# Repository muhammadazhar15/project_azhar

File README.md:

# [project_azhar](https://github.com/muhammadazhar15/project_azhar)
Collection of projects that have been made!

# [PROJECT 1: Soccer Robot Localization Based on Sensor Fusion from Odometry and Omnivision](Project1-robot_localization)

<div align="center">

</div>
  
* This research aims to create a new robot localization system for [IRIS ITS](https://iris.its.ac.id/) robots in the soccer field
* This localization system combines Odometry and Particle Filter through sensor fusion method
* Odometry uses 2 encoder sensors and a gyro sensor to sense robot displacement
* Particle Filter use omnivision as visual sensor to detect white line in the soccer field through image processing
* For more complete explanation about this research, you can check [this](Project1-robot_localization/Paper)

> **This is my early research particle filter with python**
> 
> https://user-images.githubusercontent.com/120243882/213215666-4653b4f7-5cf8-48bd-91ea-d05469076f68.mp4
> * if you want try this program you can check [this](Project1-robot_localization/Prototype_particle_filter)

> **This is particle filter that applied to the soccer robot**
> 
> https://user-images.githubusercontent.com/120243882/213215766-411f6838-0309-486a-b52c-df728a80d029.mp4

> **This is final localization system with senor fusion**
> 
> https://user-images.githubusercontent.com/120243882/213237570-8e828789-f15e-48b3-8e15-77b1aa8b0c28.mp4
> * The red line is the localization data generated by sensor fusion
> * This video compare sensor fusion data with original robot location in the soccer field

# [PROJECT 2: Voice Recognition System for Commands on Wheeled Soccer Robots](Project2-voice_command)

<div align="center">
 
 &nbsp;&nbsp;&nbsp;&nbsp;&nbsp;&nbsp;&nbsp;&nbsp;&nbsp;&nbsp;&nbsp;&nbsp;&nbsp;
   
</div>

* This research conducted to give [IRIS ITS](https://iris.its.ac.id/) soccer robots some orders through human voice
* There are 2 main processes in this voice recognition system, record and recognition
* This research use CNN (Convolutional Neural Network) to recognize commands from human voice
* There are 7 commands that can be recognized ['Corner', 'Dropball', 'Goalkick', 'Kalibrasi', 'Kickoff', 'Stop', 'Tendang']
* In this research MFCC is used as feature extraction method to process data from human voice
* Data that used in CNN training process comes from 5 different people and 9 different people for test
* For more complete explanation about this research, you can check [this](Project2-voice_command/Paper)

> **Those are some visualization data from voice signal data and MFCC feature extraction results**
> 
> 

> **Voice Commands Demo for Soccer Robot**
> 
> https://user-images.githubusercontent.com/120243882/213928835-b99e419a-455b-4ef3-9824-324b2552bdfb.mp4

# [PROJECT 3: Heart Disease Detection System with ANN (Artificial Neural Network)](Project3-heart_disease_detector)

<div align="center">
 
 &nbsp;&nbsp;&nbsp;&nbsp;&nbsp;&nbsp;&nbsp;&nbsp;
 
</div>

* Research project while teaching at [MA Darussalam Jombang](https://emispendis.kemenag.go.id/dashboard/?content=madrasah&action=lbg&nss=131235170053)
* Introducing AI (Artificial Intelligence) to Madrasah students, especially about Neural Networks
* This research was conducted with students to prepare for participate in [LKIR LIPI](https://kompetisi.brin.go.id/tentang/lkir) 2021
* Heart Disease Detection System is designed to detect disease through health status and heart sounds
* Health status data comes from [Kaggle](https://www.kaggle.com/datasets/johnsmith88/heart-disease-dataset) and heart sound data comes from [here](http://www.peterjbentley.com/heartchallenge/)
* The Heart Disease Detection System is applied in the website
* For more complete explanation about this research, you can check [this](Project3-heart_disease_detector/Paper)

> **Heart Disease Detection System Demo**
> 
> https://user-images.githubusercontent.com/120243882/213934320-be85940c-d860-4ea4-b8dd-51fb7ff6c627.mp4

# [PROJECT 4: Line Follower Robot Microcontroller](Project4-robot_line_follower)

<div align="center">
 
 &nbsp;&nbsp;&nbsp;&nbsp;&nbsp;
 
</div>

* This project is used to introduce students in [MA Darussalam Jombang](https://emispendis.kemenag.go.id/dashboard/?content=madrasah&action=lbg&nss=131235170053) about embedded systems and robotics
* This robot uses Arduino nano as microcontroller and use C/C++ programming language in Arduino IDE
* There are 3 main board in this robot: Sensor, Core, and Driver
* This line followe use 14 line sensors (consist a pair of LED and Photodiode) with switching method, only need 7 ADC to read sensors data
* In Core board, there are buttons, lcd crystal, Arduino nano, and voltage regulator to supply the required voltage for entire robotic system
* DC motor driver is used to control motors rotation, to control 2 motors need 8 MOSFET and 4 BJT Transistors

> **PCB Design for Line Sensors, Core, and DC Motor driver**
> 
> <div align="center">
>  
>  &nbsp;
>  
>  &nbsp;
>  
> </div>
> 
> * For this PCB design, you can check schematic and board with EAGLE [here](Project4-robot_line_follower/Design_PCB)
> * For simple mechanical design of this robot you can check [here](Project4-robot_line_follower/Design_mechanic)

> **Line Follower Robot Microcontroller Demo**
> 
> https://user-images.githubusercontent.com/120243882/213953569-85fc9a23-e856-4095-a18f-c3753762ad43.mp4
> * This robot can be programmed to go through certain tracks such as intersections, incline, black or white line
> * This robot also participate in [MRC 2020](https://madrasah.kemenag.go.id/mrc2020/) 

# [PROJECT 5: Transporter Robot IoT](Project5-robot_transporter_IoT)

<div align="center">
 
 &nbsp;&nbsp;&nbsp;&nbsp;
 
</div>

* This project is used to teach students before participate in [MRC 2021](https://madrasah.kemenag.go.id/mrc2021/) competition
* This Transporter Robot uses ESP32 as microcontroller and can be programmed with Arduino IDE
* Components of Transporter Robot IoT

  <table>
    <tr>
     <td>ESP32</td>
     <td>TCS3200</td>
     <td>GM66</td>
     <td>OLED 128x64</td>
     <td>Gripper Servo</td>
    </tr>
    <tr>
     <td>Line Sensor</td>
     <td>Voltage Regulator</td>
     <td>Driver Motor</td>
     <td>Gearbox Motor</td>
     <td>Lipo battery 12v</td>
    </tr>
  </table>

* There are 3 sensors used by this robot: 2 Line sensor, Barcode Sensor GM66, and Color Sensor TCS3200
* Robot mission is scaning object barcode and then send object to drop location with same barcode
* This robot also send reports about activities that have been carried out such as take the object, drop the object, and object barcode
* The report send through MQTT protocol to this [MQTT Broker Websockets](http://www.hivemq.com/demos/websocket-client/)
* You can check some simple program used to access each sensor [here](Project5-robot_transporter_IoT/Program/trial_program) and program for the entire robot system [here](Project5-robot_transporter_IoT/Program/robot)

> **Transporter Robot IoT Demo**
> 
> https://user-images.githubusercontent.com/120243882/213965095-ef7a9108-83d1-48a8-8197-9af46c50bce0.mp4

# [PROJECT 6: Smart Home IoT](Project6-smart_home_IoT)

<div align="center">
 
</div>

* This is IoT simple project to control some devices with human voice through Google Assistant
* IoT systems consist of:

  <table>
    <tr>
     <th><a href="http://esp32.net/">ESP32</a></th>
     <th><a href="https://blynk.io/">Blynk</a></th>
     <th><a href="https://ifttt.com/">IFTTT</a></th>
     <th><a href="https://assistant.google.com/">Google Assistant</a></th>
    </tr>
  </table>
  
* This project uses relay as actuator which controlled by ESP32 with Blynk interface
* IFTTT as third party, works to make connection between Blynk and Google Assistant
* Arduino IDE program for this project in [here](Project6-smart_home_IoT/Program)
* If you need more clear explanation and illustration about this system, check [here](Project6-smart_home_IoT/System_design)

> **Smart Home IoT Demo**
> 
> https://user-images.githubusercontent.com/120243882/213970831-5661dd2b-66af-45b9-8b20-814e55da1675.mp4

# [PROJECT 7: Teaching Robotics](Project7-teaching_robotics)
* These are some electronics projects that i made while teaching at MA Darussalam Jombang

<div align="center">
 
 &nbsp;&nbsp;&nbsp;&nbsp;&nbsp;&nbsp;&nbsp;&nbsp;&nbsp;&nbsp;&nbsp;&nbsp;&nbsp;&nbsp;&nbsp;&nbsp;&nbsp;&nbsp;&nbsp;&nbsp;&nbsp;&nbsp;&nbsp;&nbsp;&nbsp;&nbsp;&nbsp;
 
</div>

&nbsp;

<div align="center">
 
 &nbsp;&nbsp;
 
</div>

&nbsp;

* Flip-flop, Line sensor, Line Follower Analog, Radio Receiver, Arduino Learning Board, and Simple Motor Driver
* The purpose of these projects are to introduce students about electronics and simple robotics
* These are handbooks that I use to teach, check [here](Project7-teaching_robotics/Handbook)
* These are some collections of PCB designs that I have created to teach, check [here](Project7-teaching_robotics/Design_PCB)

# [PROJECT 8: STM32 Projects Collection](Project6-smart_home_IoT)
* These are some STM32 programming with STM32CubeMX that I had made while joining [IRIS ITS](https://iris.its.ac.id/)

<div align="center">
 
</div>

* STM32 is a family of 32-bit microcontrollers based on the ARM Cortex-M core and developed by ST Microelectronics
* STM32CubeMX uses HAL library to generate project in C programming language
* This project consists of STM32 basic programming to complex systems
* Example: GPIO, ADC, Timer, PWM, Serial, Odometry, and Robot Control
* Check my STM32 programming project [here](Project8-program_stm32/Program)

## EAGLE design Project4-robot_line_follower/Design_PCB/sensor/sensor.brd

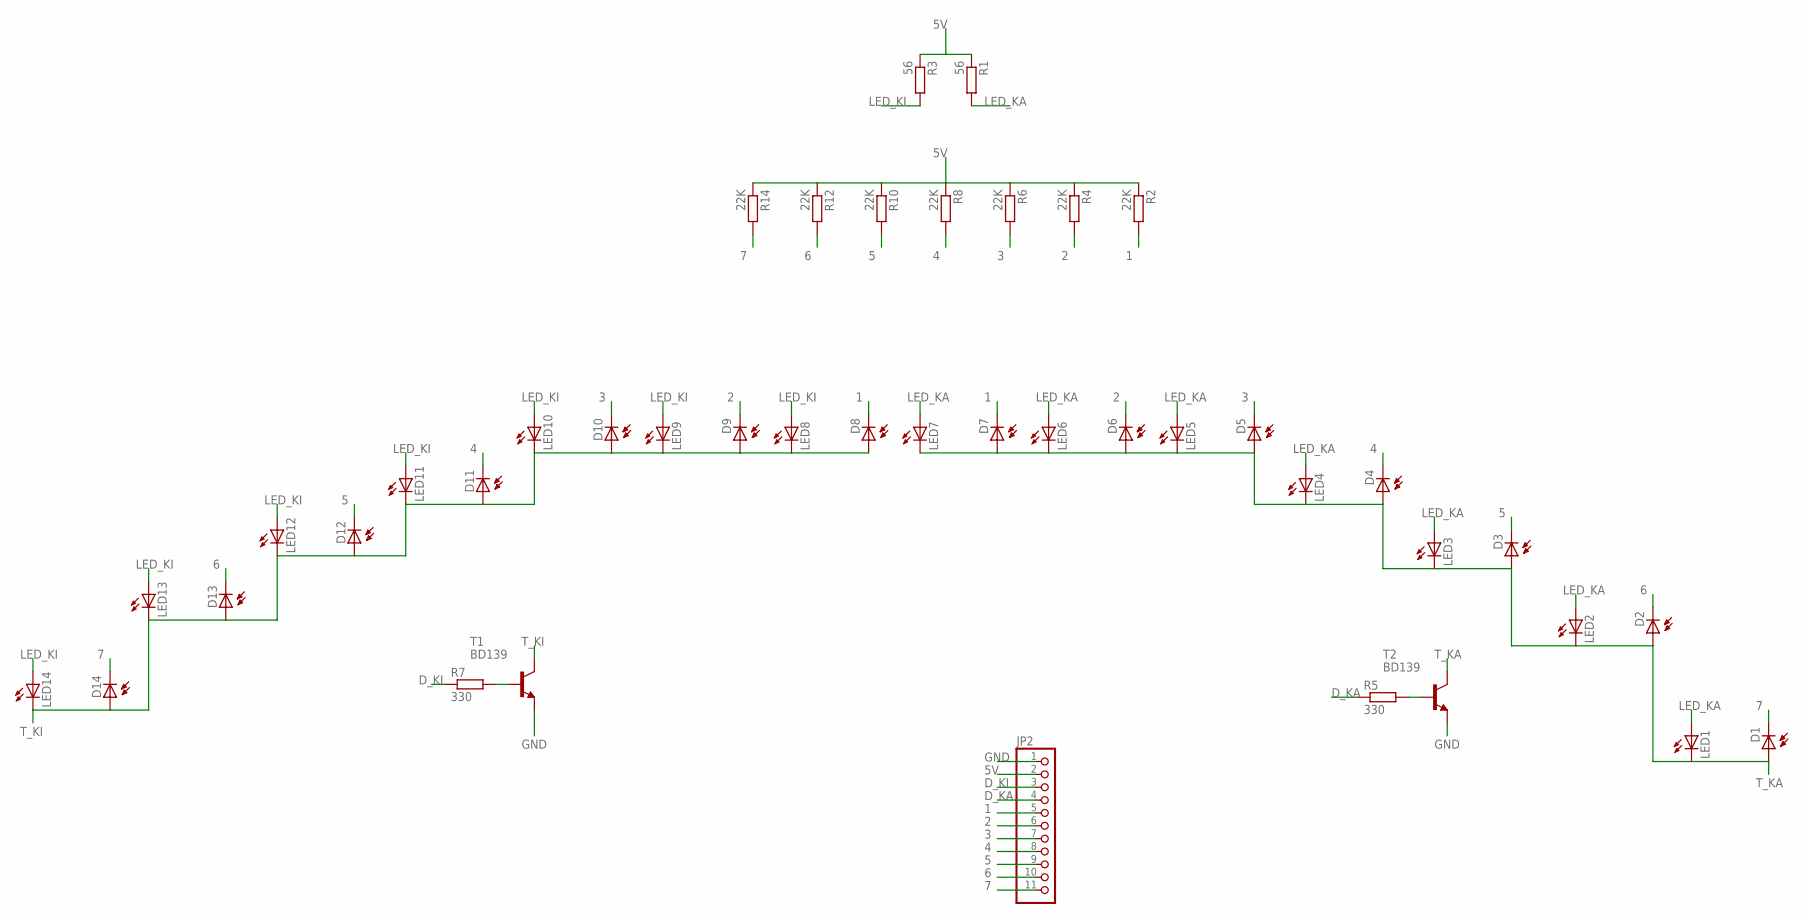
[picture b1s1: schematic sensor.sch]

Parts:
D1, D2, D3, D4, D5, D6, D7, D8, D9, D10, D11, D12, D13, D14: BPX65
JP2: PINHD-1X11; 1X11
LED1, LED2, LED3, LED4, LED5, LED6, LED7, LED8, LED9, LED10, LED11, LED12, LED13, LED14: LED3MM
R1, R3: 56; 0207/7
R2, R4, R6, R8, R10, R12, R14: 22K; 0207/7
R5, R7: 330; 0207/7
T1, T2: BD139; TO126

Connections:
1: D7.K (C), D8.K (C), JP2.5, R2.2
2: D6.K (C), D9.K (C), JP2.6, R4.2
3: D5.K (C), D10.K (C), JP2.7, R6.2
4: D4.K (C), D11.K (C), JP2.8, R8.2
5: D3.K (C), D12.K (C), JP2.9, R10.2
5V: JP2.2, R1.1, R2.1, R3.1, R4.1, R6.1, R8.1, R10.1, R12.1, R14.1
6: D2.K (C), D13.K (C), JP2.10, R12.2
7: D1.K (C), D14.K (C), JP2.11, R14.2
D_KA: JP2.4, R5.1
D_KI: JP2.3, R7.1
GND: JP2.1, T1.1 (E), T2.1 (E)
LED_KA: LED1.A, LED2.A, LED3.A, LED4.A, LED5.A, LED6.A, LED7.A, R1.2
LED_KI: LED8.A, LED9.A, LED10.A, LED11.A, LED12.A, LED13.A, LED14.A, R3.2
unnamed: R7.2, T1.3 (B)
unnamed: R5.2, T2.3 (B)
T_KA: D1.A, D2.A, D3.A, D4.A, D5.A, D6.A, D7.A, LED1.K (C), LED2.K (C), LED3.K (C), LED4.K (C), LED5.K (C), LED6.K (C), LED7.K (C), T2.2 (C)
T_KI: D8.A, D9.A, D10.A, D11.A, D12.A, D13.A, D14.A, LED8.K (C), LED9.K (C), LED10.K (C), LED11.K (C), LED12.K (C), LED13.K (C), LED14.K (C), T1.2 (C)

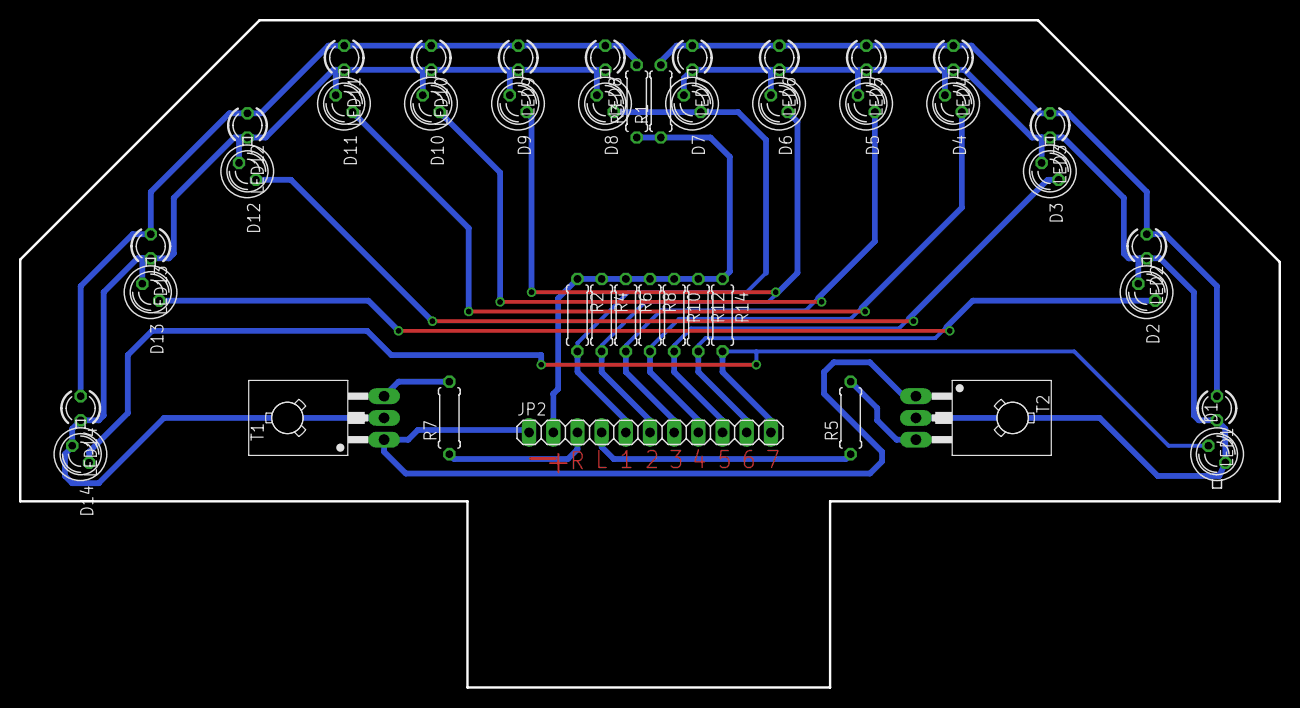
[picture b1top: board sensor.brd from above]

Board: 2 copper layers, 132.3 x 70.1 mm, 42 parts (0 on the bottom side), 17 nets.

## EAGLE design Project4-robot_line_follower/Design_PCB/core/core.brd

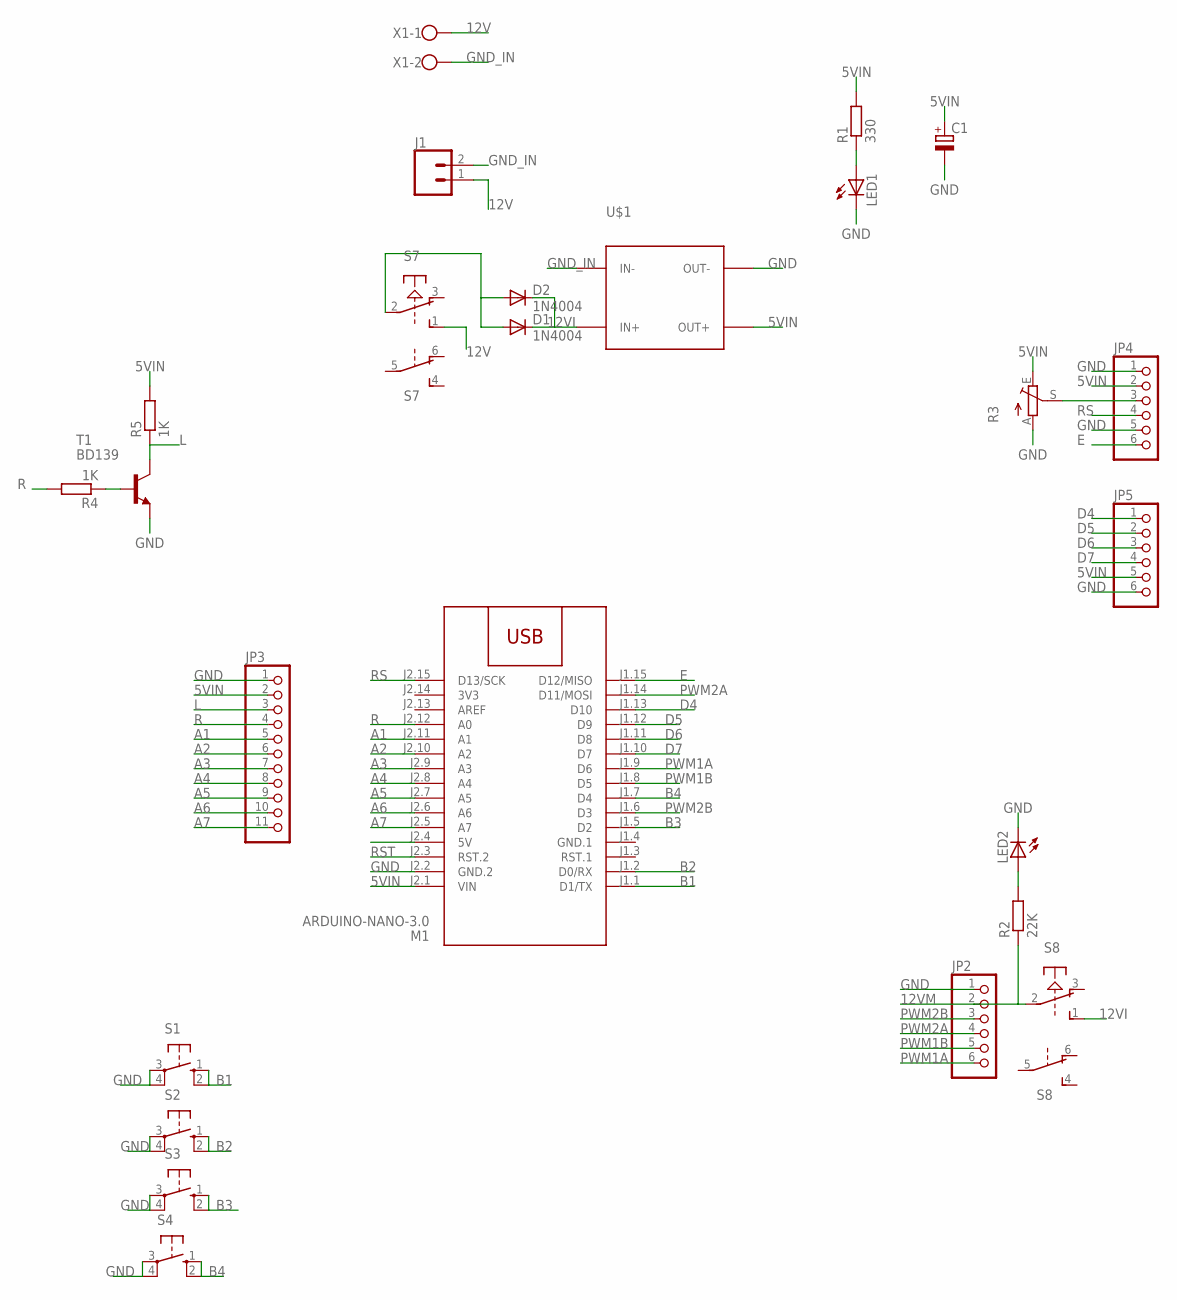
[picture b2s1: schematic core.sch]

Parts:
C1: CPOL-EUE2.5-6; E2,5-6
D1, D2: 1N4004; DO41-10
J1: CONN_02POLAR; MOLEX-1X2
JP2, JP4, JP5: PINHD-1X6; 1X06
JP3: PINHD-1X11; 1X11
LED1, LED2: LED3MM
M1: ARDUINO-NANO-3.0
R1: 330; 0207/7
R2: 22K; 0207/7
R3: TRIM_EU-CA6V; CA6V
R4, R5: 1K; 0207/7
S1, S2, S3, S4: 10-XX; B3F-10XX
S7, S8: PVA2R
T1: BD139; TO126
U$1: DC-DC-STEP-DOWN-MP2307
X1: W237-102

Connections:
3V3: M1.J2.14 (3V3)
5VIN: C1.+, JP3.2, JP4.2, JP5.5, M1.J2.1 (VIN), R1.2, R3.E, R5.2, U$1.OUT+
12V: J1.1, S7.1 (S), X1.1
12VI: D1.C, D2.C, S8.1 (S), U$1.IN+
12VM: JP2.2, R2.1, S8.2
A1: JP3.5, M1.J2.11 (A1)
A2: JP3.6, M1.J2.10 (A2)
A3: JP3.7, M1.J2.9 (A3)
A4: JP3.8, M1.J2.8 (A4)
A5: JP3.9, M1.J2.7 (A5)
A6: JP3.10, M1.J2.6 (A6)
A7: JP3.11, M1.J2.5 (A7)
B1: M1.J1.1 (D1/TX), S1.1 (S), S1.2 (S1)
B2: M1.J1.2 (D0/RX), S2.1 (S), S2.2 (S1)
B3: M1.J1.5 (D2), S3.1 (S), S3.2 (S1)
B4: M1.J1.7 (D4), S4.1 (S), S4.2 (S1)
D4: JP5.1, M1.J1.13 (D10)
D5: JP5.2, M1.J1.12 (D9)
D6: JP5.3, M1.J1.11 (D8)
D7: JP5.4, M1.J1.10 (D7)
E: JP4.6, M1.J1.15 (D12/MISO)
GND: C1.-, JP2.1, JP3.1, JP4.1, JP4.5, JP5.6, LED1.K (C), LED2.K (C), M1.J2.2 (GND.2), R3.A, S1.3, S1.4 (P1), S2.3, S2.4 (P1), S3.3, S3.4 (P1), S4.3, S4.4 (P1), T1.1 (E), U$1.OUT-
GND.1: M1.J1.4 (GND.1)
GND_IN: J1.2, U$1.IN-, X1.2
L: JP3.3, R5.1, T1.2 (C)
unnamed: D1.A, D2.A, S7.2
unnamed: LED1.A, R1.1
unnamed: LED2.A, R2.2
unnamed: R4.1, T1.3 (B)
unnamed: JP4.3, R3.S
PWM1A: JP2.6, M1.J1.9 (D6)
PWM1B: JP2.5, M1.J1.8 (D5)
PWM2A: JP2.4, M1.J1.14 (D11/MOSI)
PWM2B: JP2.3, M1.J1.6 (D3)
R: JP3.4, M1.J2.12 (A0), R4.2
RS: JP4.4, M1.J2.15 (D13/SCK)
RST: M1.J2.3 (RST.2)

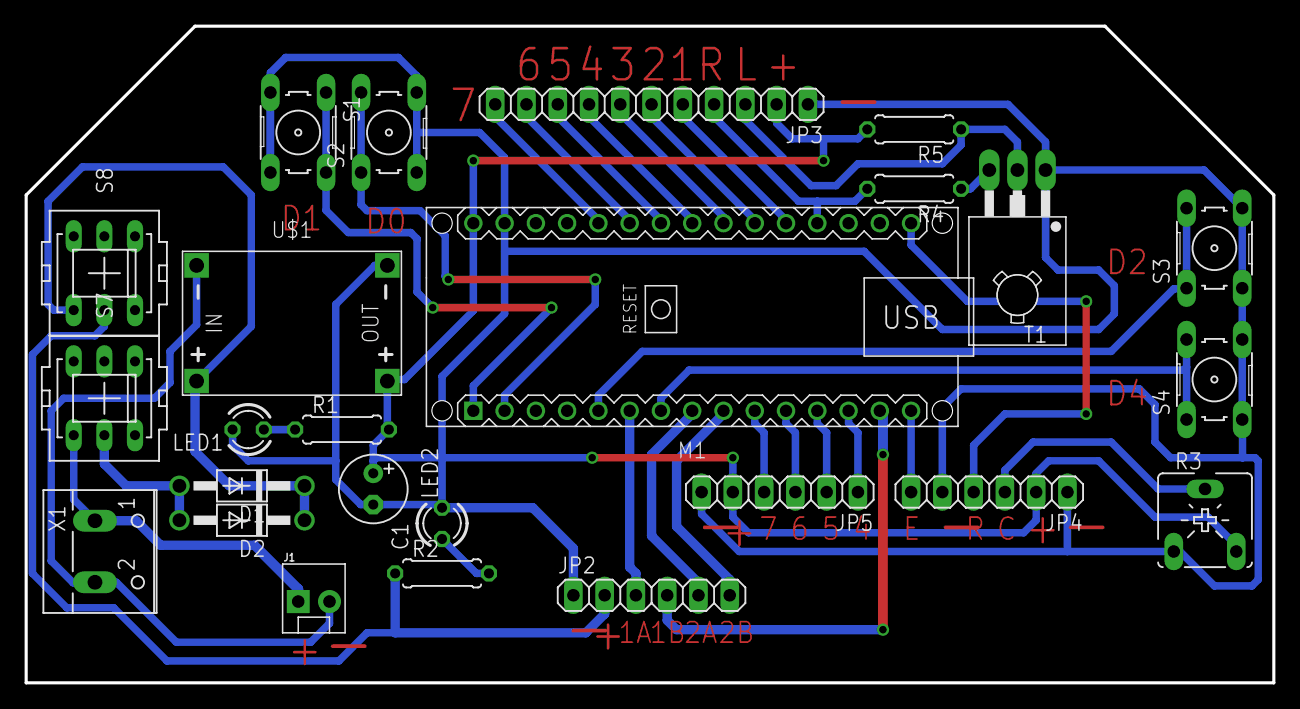
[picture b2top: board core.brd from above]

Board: 2 copper layers, 101.3 x 53.3 mm, 25 parts (0 on the bottom side), 34 nets.

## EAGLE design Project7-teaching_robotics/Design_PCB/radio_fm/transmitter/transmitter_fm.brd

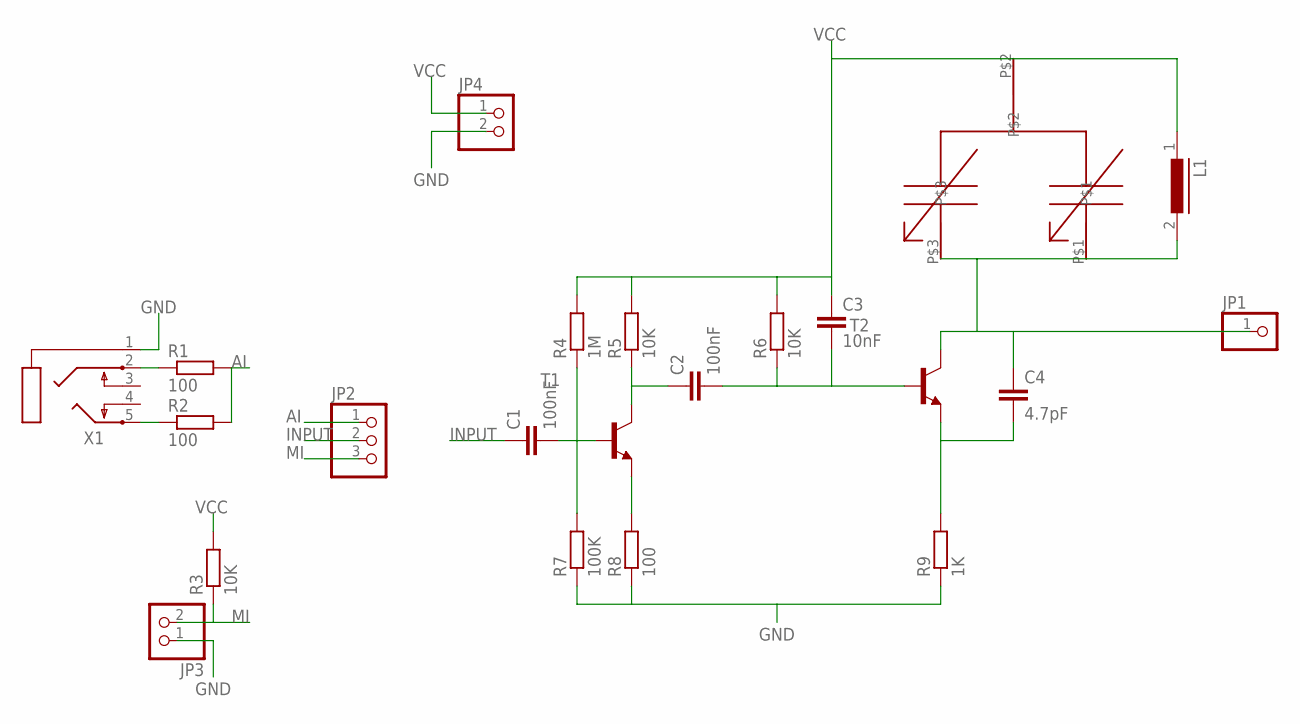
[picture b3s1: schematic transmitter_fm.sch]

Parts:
C1, C2: 100nF; C050-035X075
C3: 10nF; C050-035X075
C4: 4.7pF; C025-025X050
JP1: PINHD-1X1; 1X01
JP2: PINHD-1X3; 1X03
JP3, JP4: PINHD-1X2; 1X02
L1: DS10
R1, R2, R8: 100; 0207/7
R3, R5, R6: 10K; 0207/7
R4: 1M; 0207/7
R7: 100K; 0207/7
R9: 1K; 0207/7
T1, T2: 2N3904; TO92
U$1: VARCO_KEMATIAN_DEV; VARCO_KEMATIAN
X1: PG203J

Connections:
AI: JP2.1, R1.2, R2.2
GND: JP3.1, JP4.2, R7.1, R8.1, R9.1, X1.1
INPUT: C1.1, JP2.2
MI: JP2.3, JP3.2, R3.1
unnamed: C1.2, R4.1, R7.2, T1.2 (B)
unnamed: R8.2, T1.3 (E)
unnamed: C2.1, R5.1, T1.1 (C)
unnamed: C2.2, C3.2, R6.1, T2.2 (B)
unnamed: C4.2, R9.2, T2.3 (E)
unnamed: R2.1, X1.5
unnamed: C4.1, JP1.1, L1.2, T2.1 (C), U$1.P$1, U$1.P$3
unnamed: R1.1, X1.2
VCC: C3.1, JP4.1, L1.1, R3.2, R4.2, R5.2, R6.2, U$1.P$2

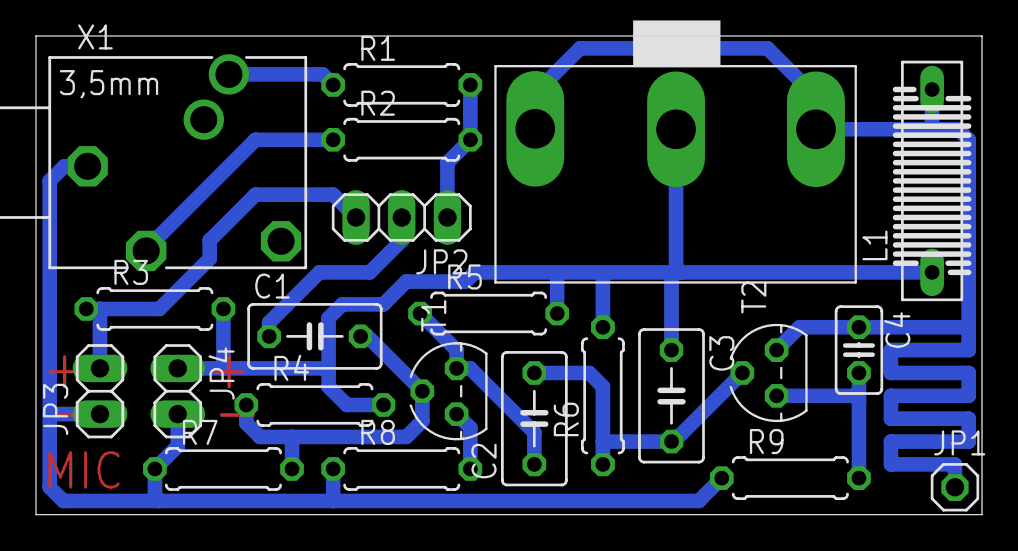
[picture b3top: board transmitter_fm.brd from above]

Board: 2 copper layers, 52.6 x 26.6 mm, 22 parts (0 on the bottom side), 13 nets.

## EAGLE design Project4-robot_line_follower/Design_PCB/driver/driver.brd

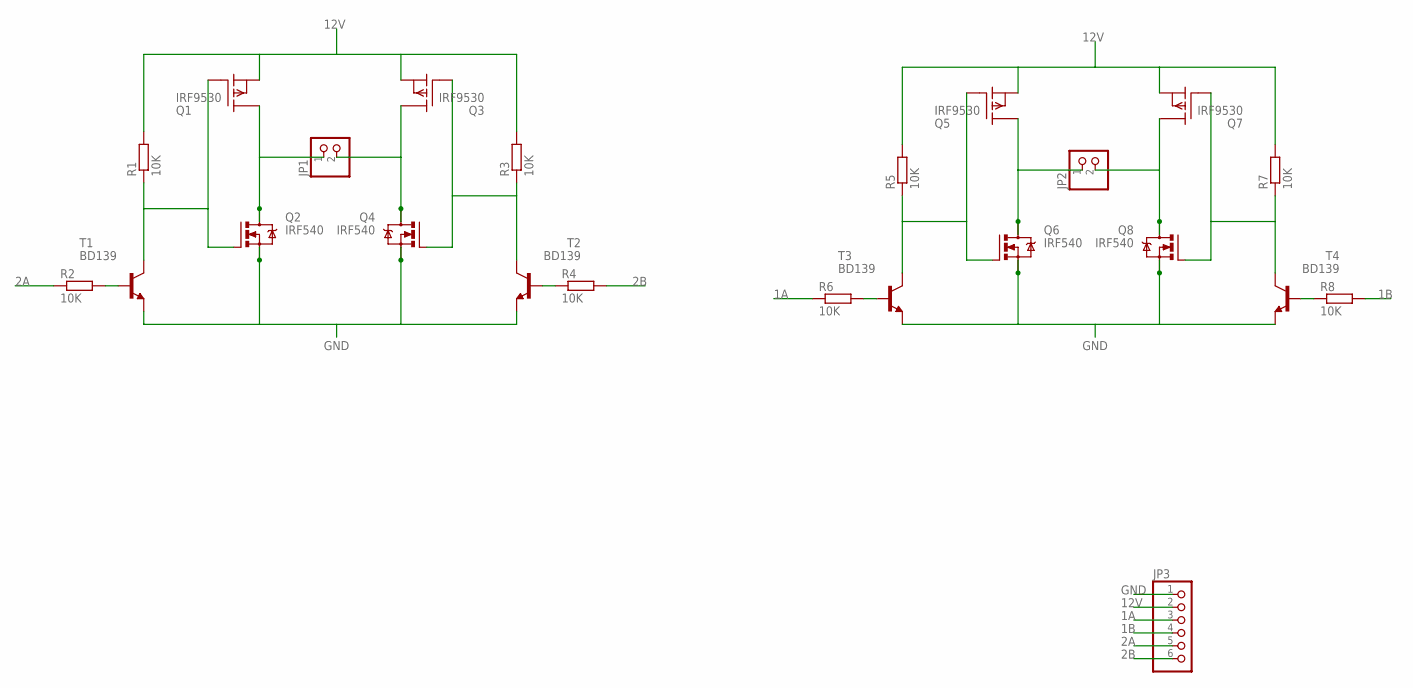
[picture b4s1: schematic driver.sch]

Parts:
JP1, JP2: PINHD-1X2; 1X02
JP3: PINHD-1X6; 1X06
Q1, Q3, Q5, Q7: IRF9530; TO220
Q2, Q4, Q6, Q8: IRF540; TO220BV
R1, R2, R3, R4, R5, R6, R7, R8: 10K; 0207/7
T1, T2, T3, T4: BD139; TO126

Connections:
1A: JP3.3, R6.1
1B: JP3.4, R8.2
2A: JP3.5, R2.1
2B: JP3.6, R4.2
12V: JP3.2, Q1.3 (S), Q3.3 (S), Q5.3 (S), Q7.3 (S), R1.2, R3.2, R5.2, R7.2
GND: JP3.1, Q2.S, Q4.S, Q6.S, Q8.S, T1.1 (E), T2.1 (E), T3.1 (E), T4.1 (E)
unnamed: JP1.1, Q1.2 (D), Q2.D
unnamed: JP1.2, Q3.2 (D), Q4.D
unnamed: JP2.1, Q5.2 (D), Q6.D
unnamed: R2.2, T1.3 (B)
unnamed: R4.1, T2.3 (B)
unnamed: Q3.1 (G), Q4.G, R3.1, T2.2 (C)
unnamed: Q1.1 (G), Q2.G, R1.1, T1.2 (C)
unnamed: JP2.2, Q7.2 (D), Q8.D
unnamed: R8.1, T4.3 (B)
unnamed: R6.2, T3.3 (B)
unnamed: Q5.1 (G), Q6.G, R5.1, T3.2 (C)
unnamed: Q7.1 (G), Q8.G, R7.1, T4.2 (C)

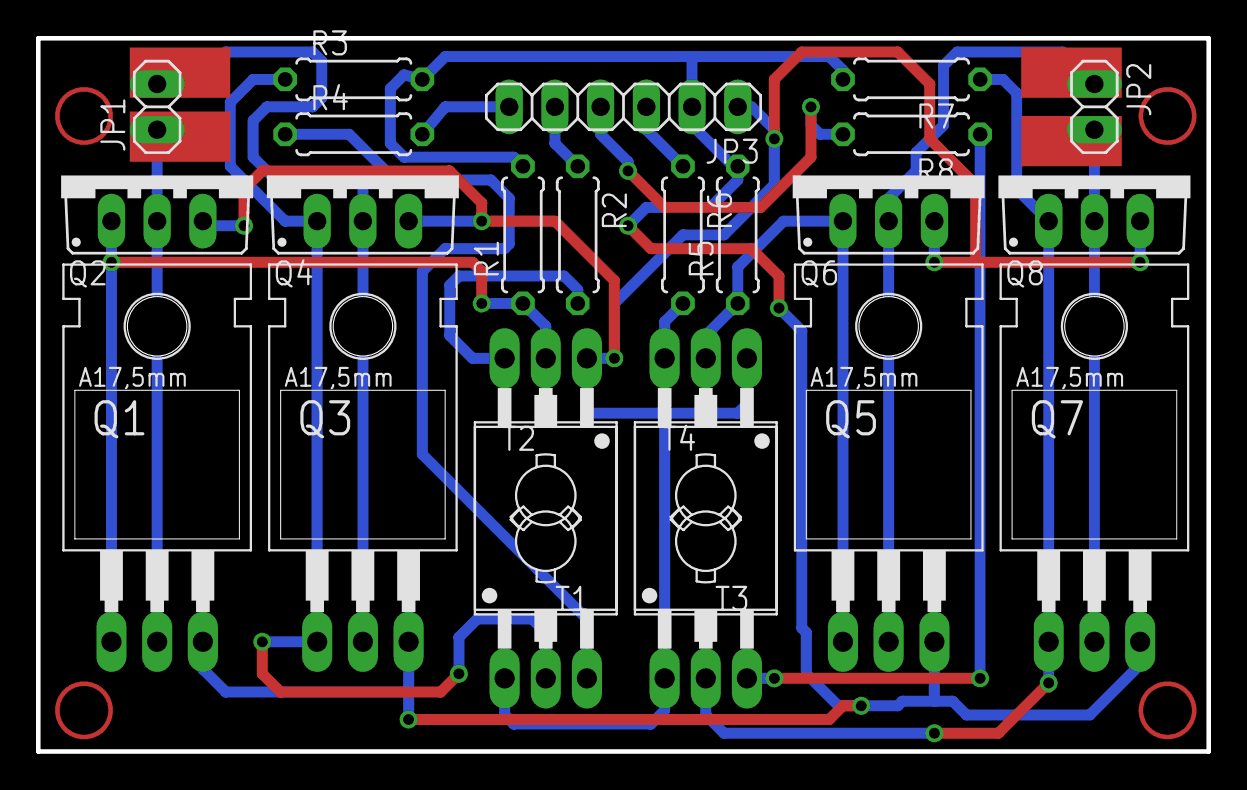
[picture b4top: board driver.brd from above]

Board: 2 copper layers, 65.0 x 39.6 mm, 23 parts (0 on the bottom side), 18 nets.

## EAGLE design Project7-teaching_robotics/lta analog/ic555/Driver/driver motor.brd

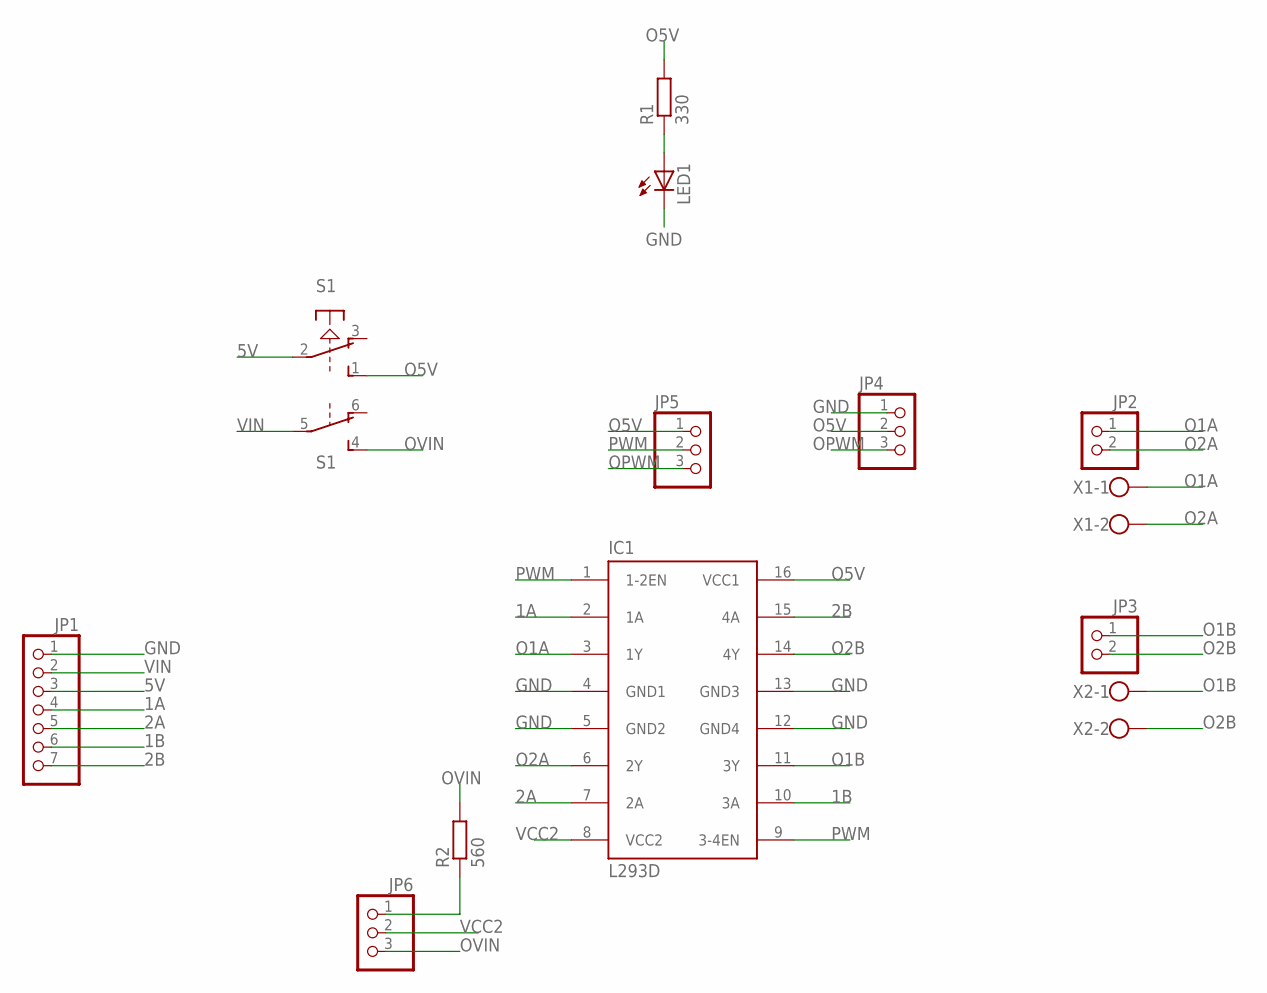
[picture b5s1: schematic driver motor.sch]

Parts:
IC1: L293D; DIL16
JP1: PINHD-1X7; 1X07
JP2, JP3: PINHD-1X2; 1X02
JP4, JP5, JP6: PINHD-1X3; 1X03
LED1: LED3MM
R1: 330; 0207/7
R2: 560; 0207/7
S1: PVA2R
X1, X2: W237-102

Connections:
1A: IC1.2 (1A), JP1.4
1B: IC1.10 (3A), JP1.6
2A: IC1.7 (2A), JP1.5
2B: IC1.15 (4A), JP1.7
5V: JP1.3, S1.2
GND: IC1.4 (GND1), IC1.5 (GND2), IC1.12 (GND4), IC1.13 (GND3), JP1.1, JP4.1, LED1.K (C)
unnamed: LED1.A, R1.1
unnamed: JP6.1, R2.1
O1A: IC1.3 (1Y), JP2.1, X1.1
O1B: IC1.11 (3Y), JP3.1, X2.1
O2A: IC1.6 (2Y), JP2.2, X1.2
O2B: IC1.14 (4Y), JP3.2, X2.2
O5V: IC1.16 (VCC1), JP4.2, JP5.1, R1.2, S1.1 (S)
OPWM: JP4.3, JP5.3
OVIN: JP6.3, R2.2, S1.4 (S)
PWM: IC1.1 (1-2EN), IC1.9 (3-4EN), JP5.2
VCC2: IC1.8 (VCC2), JP6.2
VIN: JP1.2, S1.5

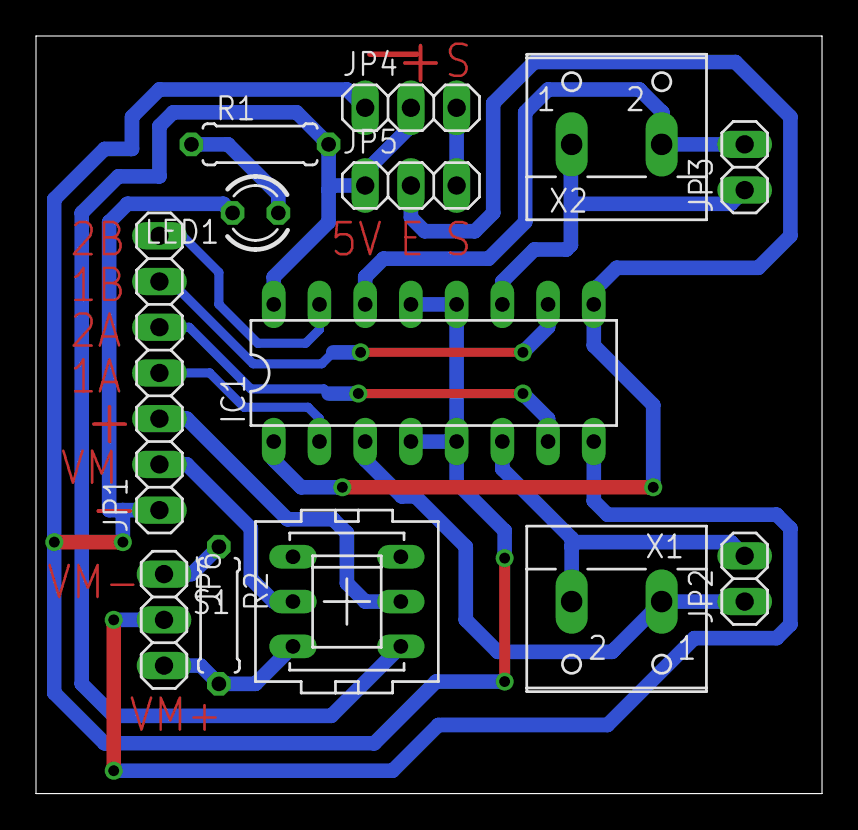
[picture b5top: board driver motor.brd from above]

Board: 2 copper layers, 43.7 x 42.1 mm, 13 parts (0 on the bottom side), 18 nets.

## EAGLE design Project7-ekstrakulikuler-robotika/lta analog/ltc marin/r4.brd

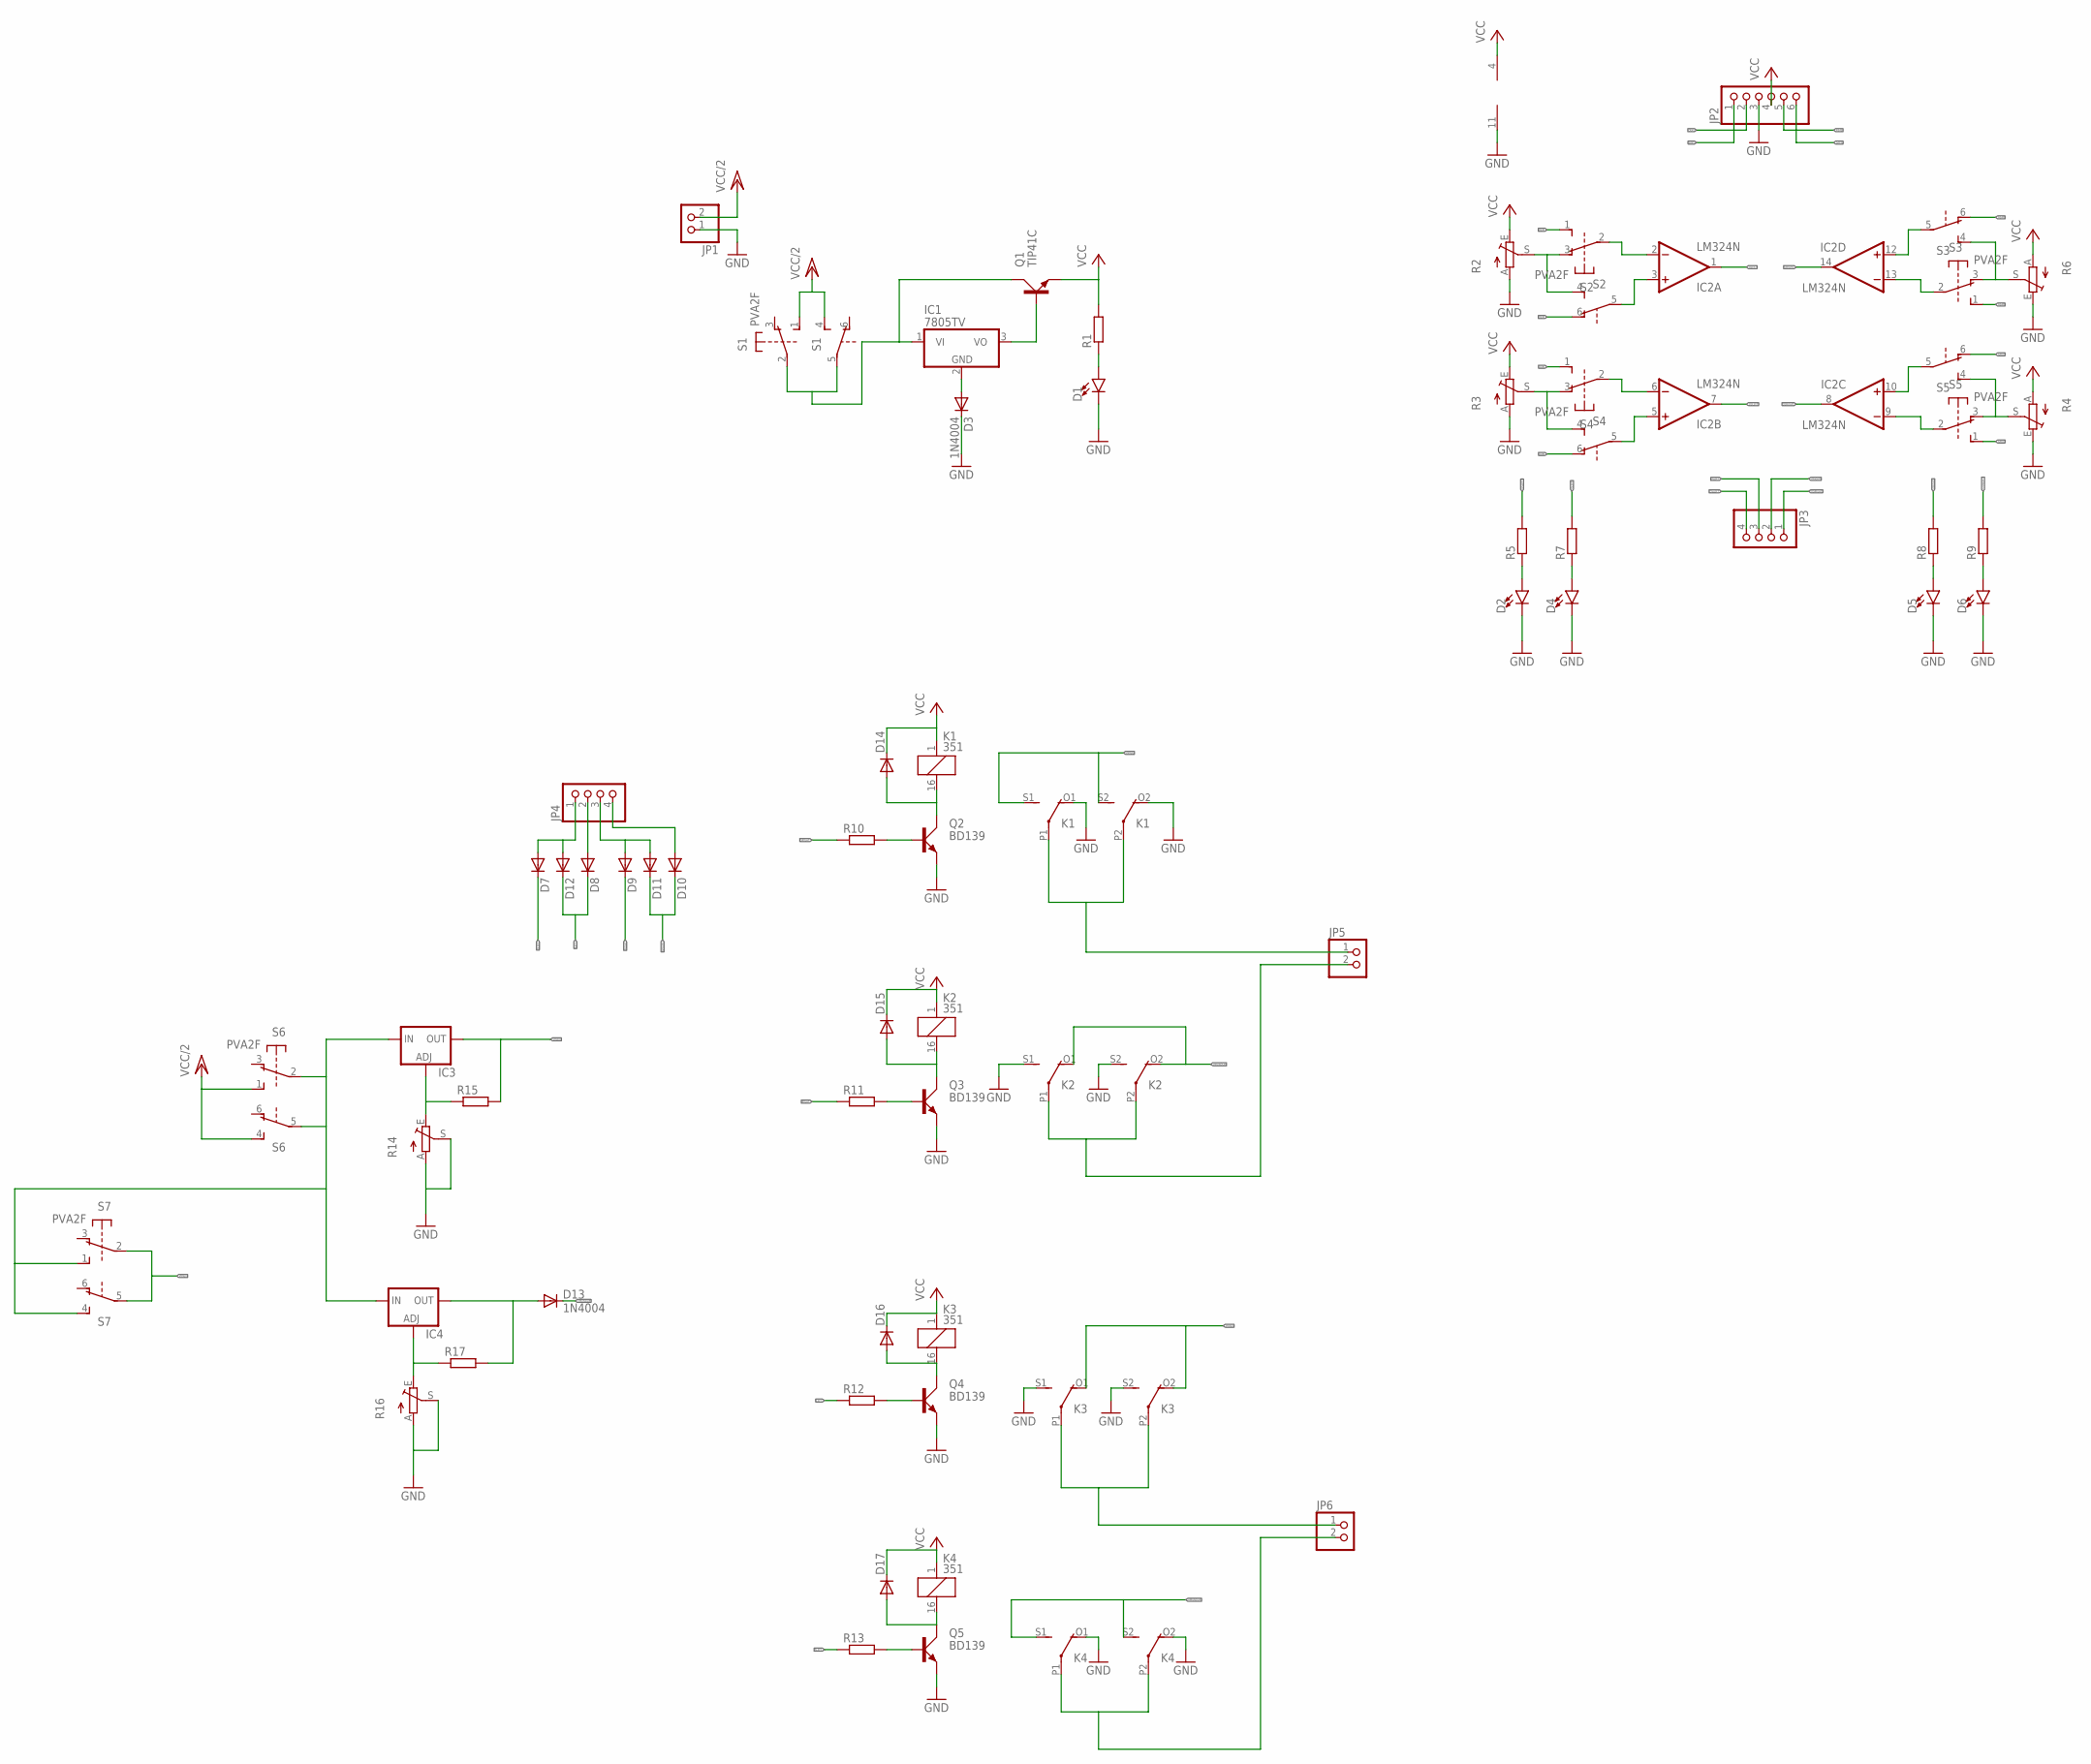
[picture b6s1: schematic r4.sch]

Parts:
D1, D2, D4, D5, D6: LED5MM; LED_5MM
D3, D13: 1N4004; DO41-10
D7, D8, D9, D10, D11, D12, D14, D15, D16, D17: 1N4148DO35-7; DO35-7
IC1: 7805TV; TO220V
IC2: LM324N; DIL14
IC3, IC4: LM317TS; 317TS
JP1, JP5, JP6: PINHD-1X2; 1X02
JP2: PINHD-1X6; 1X06
JP3, JP4: PINHD-1X4; 1X04
K1, K2, K3, K4: 351
Q1: TIP41C; TO220AV
Q2, Q3, Q4, Q5: BD139; TO126AV
R1, R5, R7, R8, R9, R10, R11, R12, R13, R15, R17: R-EU_0204/7; 0204/7
R2, R3, R4, R6, R14, R16: TRIM_EU-CA6V; CA6V
S1, S2, S3, S4, S5, S6, S7: PVA2F

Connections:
DEKI: JP2.2, S2.1 (S), S2.6 (O)
GND: D1.K (C), D2.K (C), D3.C, D4.K (C), D5.K (C), D6.K (C), IC2.11 (V-), JP1.1, JP2.3, K1.O1 (O), K1.O2 (O), K2.S1 (S), K2.S2 (S), K3.S1 (S), K3.S2 (S), K4.O1 (O), K4.O2 (O), Q2.E, Q3.E, Q4.E, Q5.E, R2.A, R3.A, R4.E, R6.E, R14.A, R14.S, R16.A, R16.S
LEFT: D8.C, D12.C, R12.1
unnamed: D3.A, IC1.2 (GND)
unnamed: IC1.1 (VI), Q1.C, S1.2, S1.5
unnamed: IC1.3 (VO), Q1.B
unnamed: D1.A, R1.1
unnamed: R2.S, S2.3 (O), S2.4 (S)
unnamed: IC2.2 (-IN), S2.2
unnamed: IC2.3 (+IN), S2.5
unnamed: R6.S, S3.3 (O), S3.4 (S)
unnamed: IC2.13 (-IN), S3.2
unnamed: IC2.12 (+IN), S3.5
unnamed: R3.S, S4.3 (O), S4.4 (S)
unnamed: IC2.6 (-IN), S4.2
unnamed: IC2.5 (+IN), S4.5
unnamed: R4.S, S5.3 (O), S5.4 (S)
unnamed: IC2.9 (-IN), S5.2
unnamed: IC2.10 (+IN), S5.5
unnamed: D2.A, R5.1
unnamed: D4.A, R7.1
unnamed: D5.A, R8.1
unnamed: D6.A, R9.1
unnamed: D7.A, D12.A, JP4.1
unnamed: D8.A, JP4.2
unnamed: D9.A, D11.A, JP4.3
unnamed: D10.A, JP4.4
unnamed: Q2.B, R10.2
unnamed: Q3.B, R11.2
unnamed: Q4.B, R12.2
unnamed: Q5.B, R13.2
unnamed: D14.A, K1.16 (2), Q2.C
unnamed: IC3.1 (ADJ), R14.E, R15.1
unnamed: IC4.1 (ADJ), R16.E, R17.1
unnamed: D15.A, K2.16 (2), Q3.C
unnamed: D16.A, K3.16 (2), Q4.C
unnamed: JP5.1, K1.P1, K1.P2
unnamed: JP5.2, K2.P1, K2.P2
unnamed: D17.A, K4.16 (2), Q5.C
unnamed: JP6.1, K3.P1, K3.P2
unnamed: JP6.2, K4.P1, K4.P2
unnamed: D13.A, IC4.2 (OUT), R17.2
unnamed: IC3.3 (IN), IC4.3 (IN), S6.2, S6.5, S7.1 (S), S7.4 (S)
unnamed: JP2.5, S3.1 (S), S3.6 (O)
OLEFT: IC2.1 (OUT), JP3.3, R7.2
ORIGHT: IC2.14 (OUT), JP3.2, R8.2
OSLEFT: IC2.7 (OUT), JP3.4, R5.2
OSRIGHT: IC2.8 (OUT), JP3.1, R9.2
RIGHT: D9.C, R11.1
SAKA: JP2.6, S5.1 (S), S5.6 (O)
SAKI: JP2.1, S4.1 (S), S4.6 (O)
SLEFT: D7.C, R13.1
SRIGHT: D10.C, D11.C, R10.1
VCC: D14.C, D15.C, D16.C, D17.C, IC2.4 (V+), JP2.4, K1.1, K2.1, K3.1, K4.1, Q1.E, R1.2, R2.E, R3.E, R4.A, R6.A
VCC/2: JP1.2, S1.1 (S), S1.4 (S), S6.1 (S), S6.4 (S)
VMAJU: IC3.2 (OUT), K1.S1 (S), K1.S2 (S), K3.O1 (O), K3.O2 (O), R15.2, S7.2, S7.5
VMUNDUR: D13.C, K2.O1 (O), K2.O2 (O), K4.S1 (S), K4.S2 (S)

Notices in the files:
parts and their libraries:
diy-modules: Released under the Creative Commons Attribution 4.0 International License: http://creativecommons.org/licenses/by/4.0
SparkFun-Retired: Licensing: Creative Commons ShareAlike 4.0 International - https://creativecommons.org/licenses/by-sa/4.0
